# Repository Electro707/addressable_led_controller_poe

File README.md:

# Addressable LED Strip Controller, POE Version
#### Rev 3 (see notes)

This is the repository for my LED strip controller. This LED controller is capable of controlling any addressable LED strip (1 or two data wires).

## Hardware Bugs

The following hardware bug exists with this version of the PCB, which will be addessed in the next revision:
- The LED data pin, IO35, is input only. Use IO32/CLK for now.
- The traces to IO16, IO17 are connected to something. Must have trace cut out.
- `E_INT` must be connected to GP0, and disconnected from IO18
- `E_RST` should be pulled down, not up
- `LED2` should have a dedicated pulldown resistor.
- The PHY chip will oscillate even if RESET is held low. Thus to turn on the strip, one must reset the ESP32 randomly until it boots

## Firmware

This controller uses the [WLED firmware](https://github.com/Aircoookie/WLED). Instructions to upload the firmware unto the board can be found on their webpage.

For this revision, there is a modified version of WLED to enable Ethernet. The diff is in [docs/rev3_patch.diff](docs/rev3_patch.diff), which is applied to commit `1dab26bcbcac051f2b7be47a2d5c757a9938bf1f`

Thru J2, you can connect an ESP32 programmer such as the ESP-Prog. You can also make your own "automatic downloader" (i.e not requiring to reset the device and selecting boot mode when uploading) circuit. Details of which can be found on Espressif's ESP-Prog docs on [Automatic Downloading Function](https://espressif-docs.readthedocs-hosted.com/projects/espressif-esp-iot-solution/en/latest/hw-reference/ESP-Prog_guide.html#automatic-downloading-function).

## Revisioning

This version was originally a continuation of my original LED controller, over at [https://github.com/Electro707/addressable_led_controller](https://github.com/Electro707/addressable_led_controller), where it was given a Rev 3 revision.

Since then, I have made another smaller non-POE controller, and thus decided to split this project into it's own repository. And thus Rev 1 and 2 does not exist for this variant, and everything starts from Rev 3.

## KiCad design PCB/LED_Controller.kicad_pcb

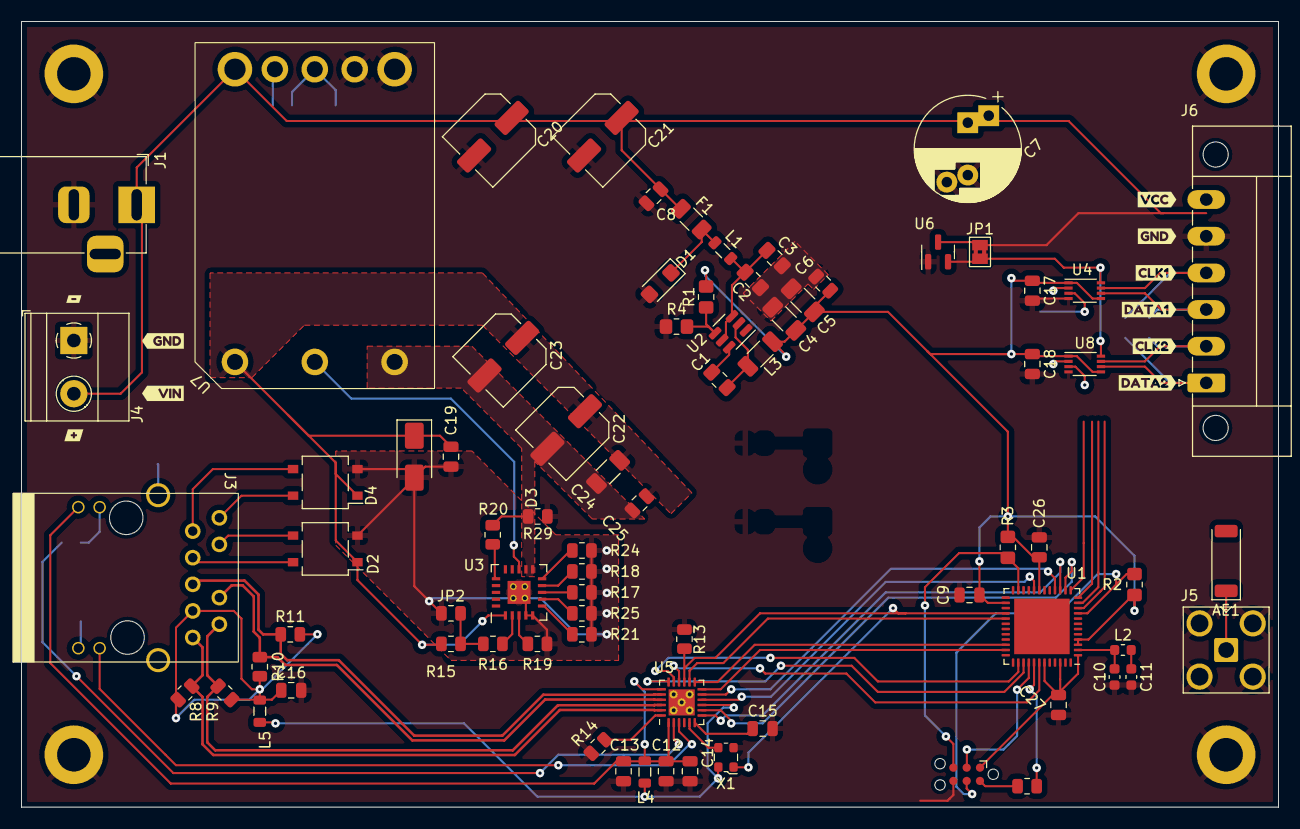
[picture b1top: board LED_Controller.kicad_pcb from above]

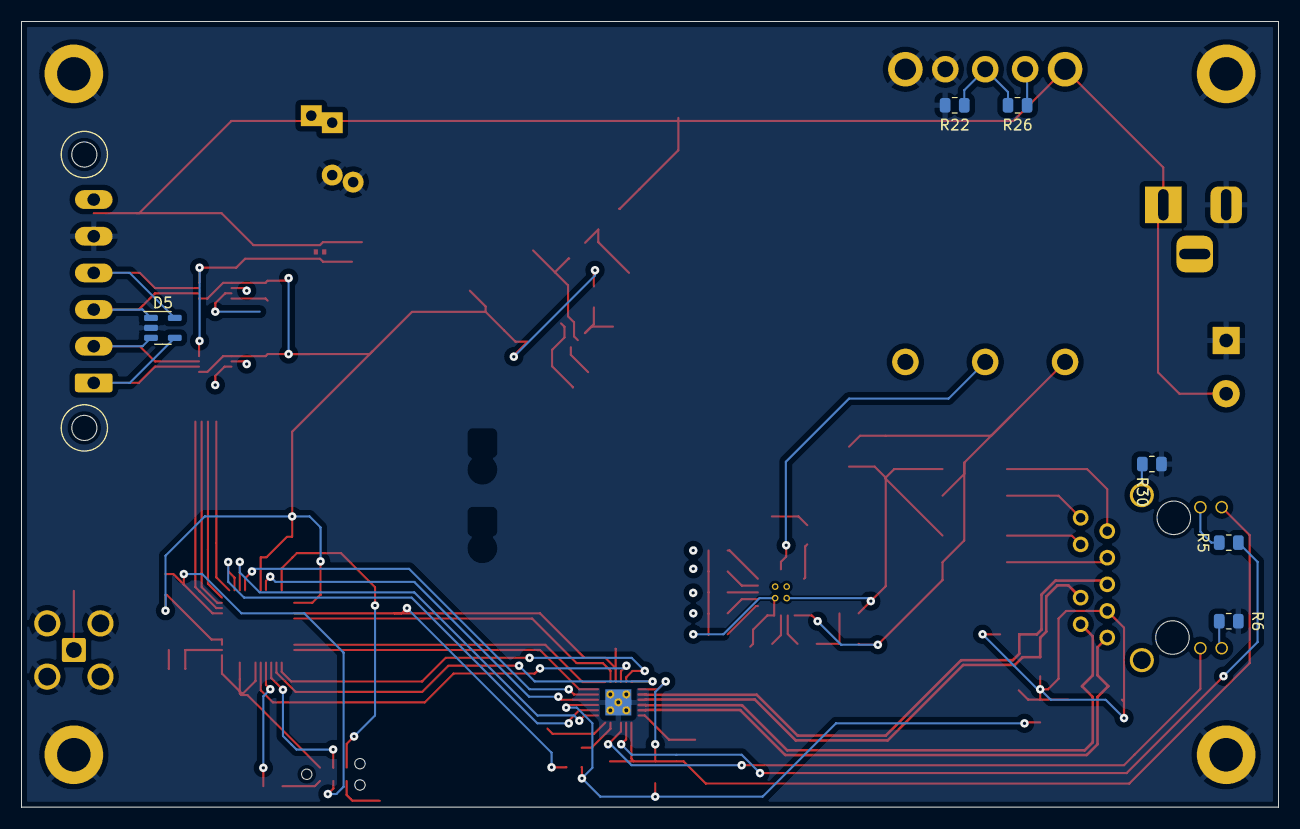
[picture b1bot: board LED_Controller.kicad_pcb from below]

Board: 2 copper layers, 120.0 x 75.0 mm, 96 parts (6 on the bottom side), 63 nets.

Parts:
AE1: Antenna_Chip; Johanson_2450AT43F0100
C1, C2: 0.1uF; C_0805_2012Metric_Pad1.18x1.45mm_HandSolder
C3: 10uF; C_0805_2012Metric_Pad1.18x1.45mm_HandSolder
C4: 10uF; C_1206_3216Metric_Pad1.33x1.80mm_HandSolder
C5: 22uF; C_1206_3216Metric_Pad1.33x1.80mm_HandSolder
C6, C8: 0.1uF; C_0805_2012Metric
C7: 1000uF; CP_Radial_D10.0mm_P5.00mm_P7.50mm
C9, C17, C18, C19, C25, C26, C27: 0.1u; C_0805_2012Metric
C10: 2.2pF; C_0603_1608Metric
C11: 4pF; C_0603_1608Metric
C12, C13, C14, C15, C16: 1uF; C_0805_2012Metric
C20: 330uF; C_Elec_6.3x5.4
C21: 0.1u; C_Elec_6.3x5.4
C22: 100uF; C_Elec_6.3x5.4
C23: 100uF; C_Elec_6.3x5.8
C24: 1uF; C_1206_3216Metric_Pad1.33x1.80mm_HandSolder
D1: SMF15A; D_SMF
D2, D4: CDBHM220L; TO-269AA
D3: SMAJ58A; D_SMA
D5: SP0504BAHT; SOT-23-5
F1: Polyfuse; Fuse_1206_3216Metric
H1, H2, H3, H4: MountingHole_Pad; MountingHole_3.2mm_M3_DIN965_Pad
J1: Barrel_Jack; BarrelJack_Horizontal
J2: Conn_01x06_Female; Tag-Connect_TC2030-IDC-NL_2x03_P1.27mm_Vertical
J3: 74984104400
J4: Screw_Terminal_01x02; TerminalBlock_Phoenix_MKDS-1,5-2-5.08_1x02_P5.08mm_Horizont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
J5: Conn_Coaxial; SMA_Amphenol_901-143_Horizontal
J6: Screw_Terminal_01x06; PhoenixContact_MC_1,5_6-GF-3.5_1x06_P3.50mm_Horizontal_Thre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
JP1: Jumper_2_Bridged; SolderJumper-2_P1.3mm_Bridged2Bar_Pad1.0x1.5mm
JP2: Jumper_2_Bridged; R_0805_2012Metric
L1, L4, L5: L_Ferrite; L_0805_2012Metric
L2: 2.2nH; L_0603_1608Metric
L3: 3.3uH; L_1206_3216Metric_Pad1.22x1.90mm_HandSolder
R1: 31.6k; R_0805_2012Metric_Pad1.20x1.40mm_HandSolder
R2, R3, R4: 10k; R_0805_2012Metric_Pad1.20x1.40mm_HandSolder
R5, R6: 1k; R_0805_2012Metric
R7: 470; R_0805_2012Metric
R8, R9, R10, R11: 49.9; R_0805_2012Metric
R13: 10k; R_0805_2012Metric
R14: 12.1k; R_0805_2012Metric
R15: 13k; R_0805_2012Metric
R16: 12k; R_0805_2012Metric
R17: 1.3k; R_0805_2012Metric
R18, R20, R24, R29, R30: 0; R_0805_2012Metric
R19: 63.4; R_0805_2012Metric
R21: 249; R_0805_2012Metric
R22, R26: R; R_0805_2012Metric
R25: 49.9k; R_0805_2012Metric
U1: ESP32-PICO-D4; QFN-48-1EP_7x7mm_P0.5mm_EP5.3x5.3mm
U2: AP62200WU-7; TSOT-23-6
U3: TPS2372; TI_RGW0020B
U4, U8: 74LVCH2T45DC; VSSOP-8_2.3x2mm_P0.5mm
U5: LAN8720A; VQFN-24-1EP_4x4mm_P0.5mm_EP2.5x2.5mm_ThermalVias
U6: MCP1792x-5002xCB; SOT-23
U7: VCB4805SBO-50WR3
X1: ECS-2520MV-xxx-xx; Oscillator_SMD_ECS_2520MV-xxx-xx-4Pin_2.5x2.0mm
kibuzzard-64D45DDA: G***; kibuzzard-64D45DDA
kibuzzard-6599B9E0: G***; kibuzzard-6599B9E0
kibuzzard-6599B9EA: G***; kibuzzard-6599B9EA
kibuzzard-6599B9F1: G***; kibuzzard-6599B9F1
kibuzzard-6599BA4A: G***; kibuzzard-6599BA4A
kibuzzard-6599BA32: G***; kibuzzard-6599BA32
kibuzzard-6599BA38: G***; kibuzzard-6599BA38
kibuzzard-6599BAF9: G***; kibuzzard-6599BAF9
kibuzzard-6599BB04: G***; kibuzzard-6599BB04
kibuzzard-6599BB10: G***; kibuzzard-6599BB10

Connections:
+3V3: C4.1, C5.1, C6.1, C9.1, C17.1, C18.1, C26.1, C27.1, J2.1, L3.2, L4.2, L5.2, R1.2, R2.1, R3.1, U1.1 (VDDA), U1.3 (VDDA3P3), U1.4 (VDDA3P3), U1.19 (VDD3P3_RTC), U1.26 (VDD_SDIO), U1.37 (VDD3P3_CPU), U1.43 (VDDA), U1.46 (VDDA), U4.1 (VCCA), U4.5 (DIR), U5.9 (VDDIO), U8.1 (VCCA), U8.5 (DIR), X1.4 (VDD)
+5V: JP1.2 (B), U4.8 (VCCB), U6.2 (VO), U8.8 (VCCB)
/EN: J2.4, R2.2, U1.9 (EN)
/E_CRS_DV: U1.16 (IO27), U5.11 (CRS_DV/MODE2)
/E_MDC: U1.34 (IO5), U5.13 (MDC)
/E_MDIO: U1.35 (IO18), U5.12 (MDIO)
/E_RXD0: U1.14 (IO25), U5.8 (RXD0/MODE0)
/E_RXD1: U1.15 (IO26), U5.7 (RXD1/MODE1)
/E_RXER: U1.20 (IO13), U5.10 (RXER/PHYAD0)
/E_TXD0: U1.38 (IO19), U5.17 (TXD0)
/E_TXD1: U1.39 (IO22), U5.18 (TXD1)
/E_TXEN: U1.42 (IO21), U5.16 (TXEN)
/E_~INT: U1.29 (SD3/IO10), U5.14 (~INT/REFCLKO)
/E_~RST: R13.2, U1.28 (SD2/IO9), U5.15 (~RST), X1.1 (Tri-State)
/Ethernet and Connector/ETH_LED1: J3.11, U5.3 (LED1/REGOFF)
/Ethernet and Connector/ETH_LED2: R5.2, U5.2 (LED2/~INTSEL)
/Ethernet and Connector/ETH_RX+: J3.4 (RD+), R10.2, U5.21 (TXP)
/Ethernet and Connector/ETH_RX-: J3.5 (RD-), R11.2, U5.20 (TXN)
/Ethernet and Connector/ETH_TX+: J3.1 (TD+), R8.2, U5.23 (RXP)
/Ethernet and Connector/ETH_TX-: J3.2 (TD-), R9.2, U5.22 (RXN)
/Ethernet and Connector/ETH_V1+: D2.4, J3.7 (V1+)
/Ethernet and Connector/ETH_V1-: D2.3, J3.8 (V1-)
/Ethernet and Connector/ETH_V2+: D4.3, J3.9 (V2+)
/Ethernet and Connector/ETH_V2-: D4.4, J3.10 (V2-)
/GPIO0: J2.5, R3.2, U1.23 (IO0), U5.5 (XTAL1/CLKIN), X1.3 (OUT)
/LED1-CLK_{H}: D5.5 (K), J6.4, U4.7 (1B)
/LED1-CLK_{L}: U1.12 (IO32), U4.2 (1A)
/LED1-DATA_{H}: D5.1 (K), J6.3, U4.6 (2B)
/LED2-CLK_{H}: D5.3 (K), J6.2, U8.7 (1B)
/LED2-DATA_{H}: D5.4 (K), J6.1, U8.6 (2B)
/RX: J2.3, U1.40 (U0RXD/IO3)
/TX: R7.1, U1.41 (U0TXD/IO1)
GND: C2.2, C3.2, C4.2, C5.2, C6.2, C7.2, C8.2, C9.2, C10.2, C11.2, C12.2, C13.2, C14.2, C15.2, C16.2, C17.2, C18.2, C20.2, C21.2, C26.2, C27.2, D1.2 (A2), D5.2 (A), H1.1, H2.1, H3.1, H4.1, J1.2, J2.6, J4.1, J5.2 (Ext), J6.5, R4.1, R6.2, R13.1, R14.2, R22.1, R29.1, R30.2, U1.49 (GND), U2.1 (GND), U4.4 (GND), U5.25 (VSS), U6.1 (GND), U7.4 (0v), U7.5 (Sense-), U8.4 (GND), X1.2 (GND)
unnamed: AE1.1 (FEED), C11.1, J5.1 (In), L2.2
unnamed: D1.1 (A1), F1.2, L1.1
unnamed: C19.1, C22.1, C23.1, C24.1, C25.1, D2.1 (+), D3.1 (A1), D4.1 (+), R15.1, U3.1 (VDD), U7.1 (Vin)
unnamed: C19.2, D2.2 (-), D3.2 (A2), D4.2 (-), JP2.1 (A), R17.1, R18.1, R19.1, R21.1, R24.1, R25.1, U3.4 (VSS), U3.5 (VSS), U3.21 (PAD)
unnamed: J2.2, R7.2
unnamed: C16.1, J3.3 (CD), L5.1, R8.1, R9.1, R10.1, R11.1
unnamed: J3.12, R6.1
unnamed: J3.13, R5.1
unnamed: J3.SH, R30.1
unnamed: JP2.2 (B), R15.2, R16.1
unnamed: C10.1, L2.1, U1.2 (LNA_IN)
unnamed: C1.1, U2.6 (BST)
unnamed: C2.1, C3.1, L1.2, U2.3 (VIN), U2.5 (EN)
unnamed: R1.1, R4.2, U2.4 (FB)
unnamed: C1.2, L3.1, U2.2 (SW)
unnamed: R17.2, U3.8 (AMPS_CTL)
unnamed: R19.2, U3.3 (CLSA)
unnamed: R21.2, U3.6 (CLSB)
unnamed: R16.2, U3.2 (DEN)
unnamed: R20.1, U3.16 (IRSHDL_EN)
unnamed: R18.2, U3.9 (MPS_DUTY)
unnamed: U3.13 (PG), U7.2 (CTRL)
unnamed: R25.2, U3.7 (REF)
unnamed: R24.2, U3.10 (~AUTCLS)
unnamed: R14.1, U5.24 (RBIAS)
unnamed: C15.1, U5.6 (VDDCR)
unnamed: C22.2, C23.2, C24.2, C25.2, R20.2, R29.2, U3.11 (RTN), U3.12 (RTN), U7.3 (GND)
unnamed: R22.2, R26.2, U7.6 (Trim)
VIN: C7.1, C8.1, C20.1, C21.1, F1.1, J1.1, J4.2, J6.6, JP1.1 (A), R26.1, U6.3 (VI), U7.7 (Sense+), U7.8 (+V)
Vdda2: C12.1, C13.1, C14.1, J3.14, L4.1, U5.1 (VDD2A), U5.19 (VDD1A)

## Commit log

2024-09-09 Initial commit for this project
